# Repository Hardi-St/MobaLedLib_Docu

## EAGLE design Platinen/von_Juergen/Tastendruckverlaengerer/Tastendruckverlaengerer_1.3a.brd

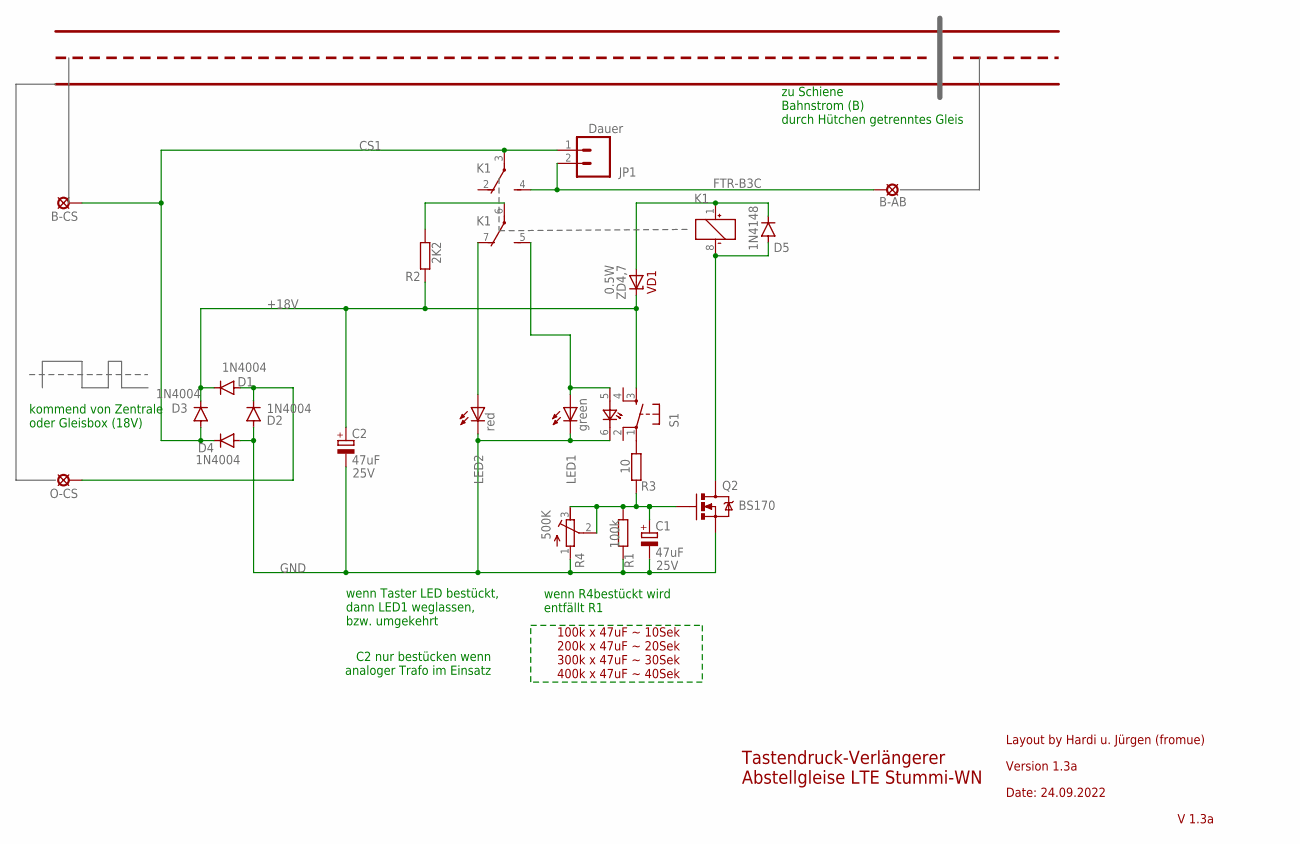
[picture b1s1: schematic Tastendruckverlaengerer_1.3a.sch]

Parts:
B-AB: SE14
B-CS: SE14
C1, C2: 47uF; TT2D5L
D1, D2, D3, D4: 1N4004; DO41-10A
D5: 1N4148; DO35-7
JP1: Dauer; 1X02
K1: FTR-B3C; FTR-B4C
LED1: green; LED3MM
LED2: red; LED3MM
O-CS: SE14
Q2: BS170; TO-92
R1: 100k; 0204/7
R2: 2K2; 0204/7
R3: 10; 0204/7
R4: 500K; RTRIM3296W
S1: TASTER_LEDTC-1198-B; TASTER_LED
VD1: ZD4,7; DIODES-ZENER_DO35-7; MOUSER ZF4.7

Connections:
+18V: C2.+, D1.C, D3.C, R2.2, S1.3 (S), VD1.C
CS1: B-CS.MP, D3.A, D4.C, JP1.1, K1.3
GND: C1.-, C2.-, D2.A, D4.A, LED1.K (C), LED2.K (C), Q2.3 (S), R1.2, R4.1 (A), S1.6 (-)
unnamed: K1.6, R2.1
unnamed: K1.5 (S), LED1.A, S1.5 (+)
unnamed: K1.7 (O), LED2.A
unnamed: D5.C, K1.1 (+), VD1.A
unnamed: C1.+, Q2.2 (G), R1.1, R3.2, R4.2 (S), R4.3 (E)
unnamed: D5.A, K1.8 (-), Q2.1 (D)
unnamed: D1.A, D2.C, O-CS.MP
unnamed: B-AB.MP, JP1.2, K1.4 (S)
TAST: R3.1, S1.1

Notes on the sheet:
kommend von Zentrale oder Gleisbox (18V)
zu Schiene Bahnstrom (B) durch Hütchen getrenntes Gleis
Tastendruck-Verlängerer Abstellgleise LTE Stummi-WN
Layout by Hardi u. Jürgen (fromue)
Version 1.3a
Date: 24.09.2022
V 1.3a
100k x 47uF ~ 10Sek 200k x 47uF ~ 20Sek 300k x 47uF ~ 30Sek 400k x 47uF ~ 40Sek
wenn R4bestückt wird entfällt R1
wenn Taster LED bestückt, dann LED1 weglassen, bzw. umgekehrt
C2 nur bestücken wenn analoger Trafo im Einsatz

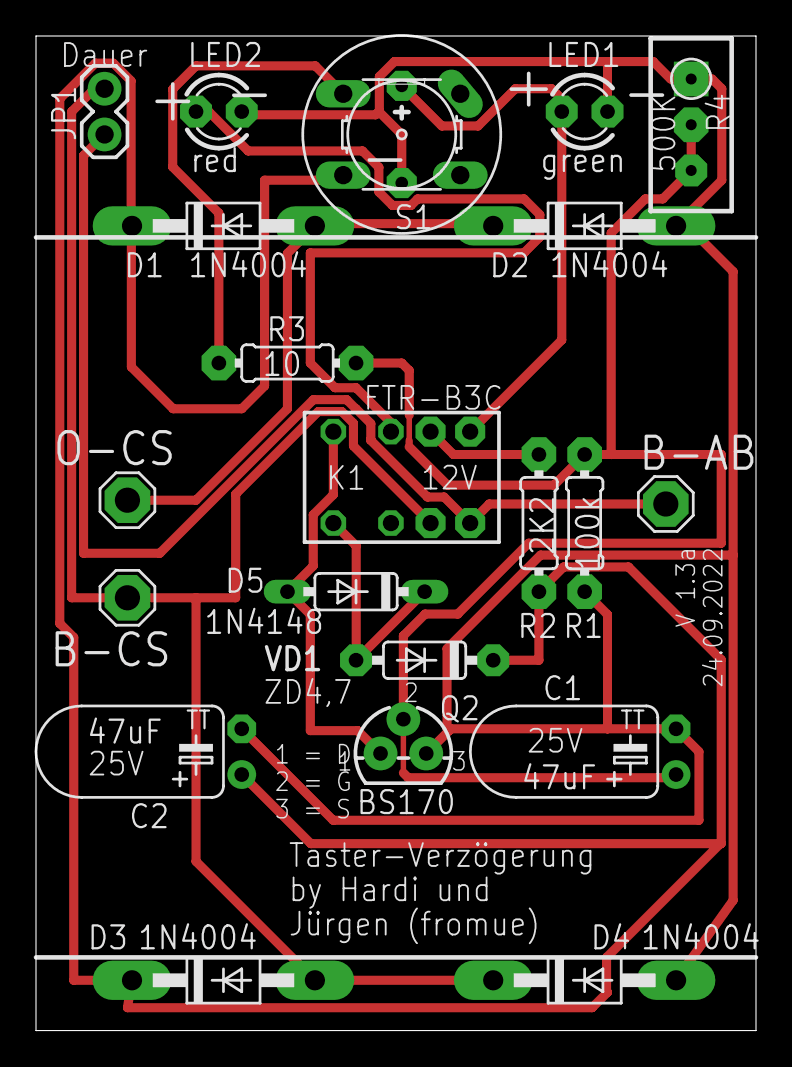
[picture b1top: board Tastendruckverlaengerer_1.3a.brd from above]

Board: 2 copper layers, 40.0 x 55.3 mm, 21 parts (0 on the bottom side), 12 nets.

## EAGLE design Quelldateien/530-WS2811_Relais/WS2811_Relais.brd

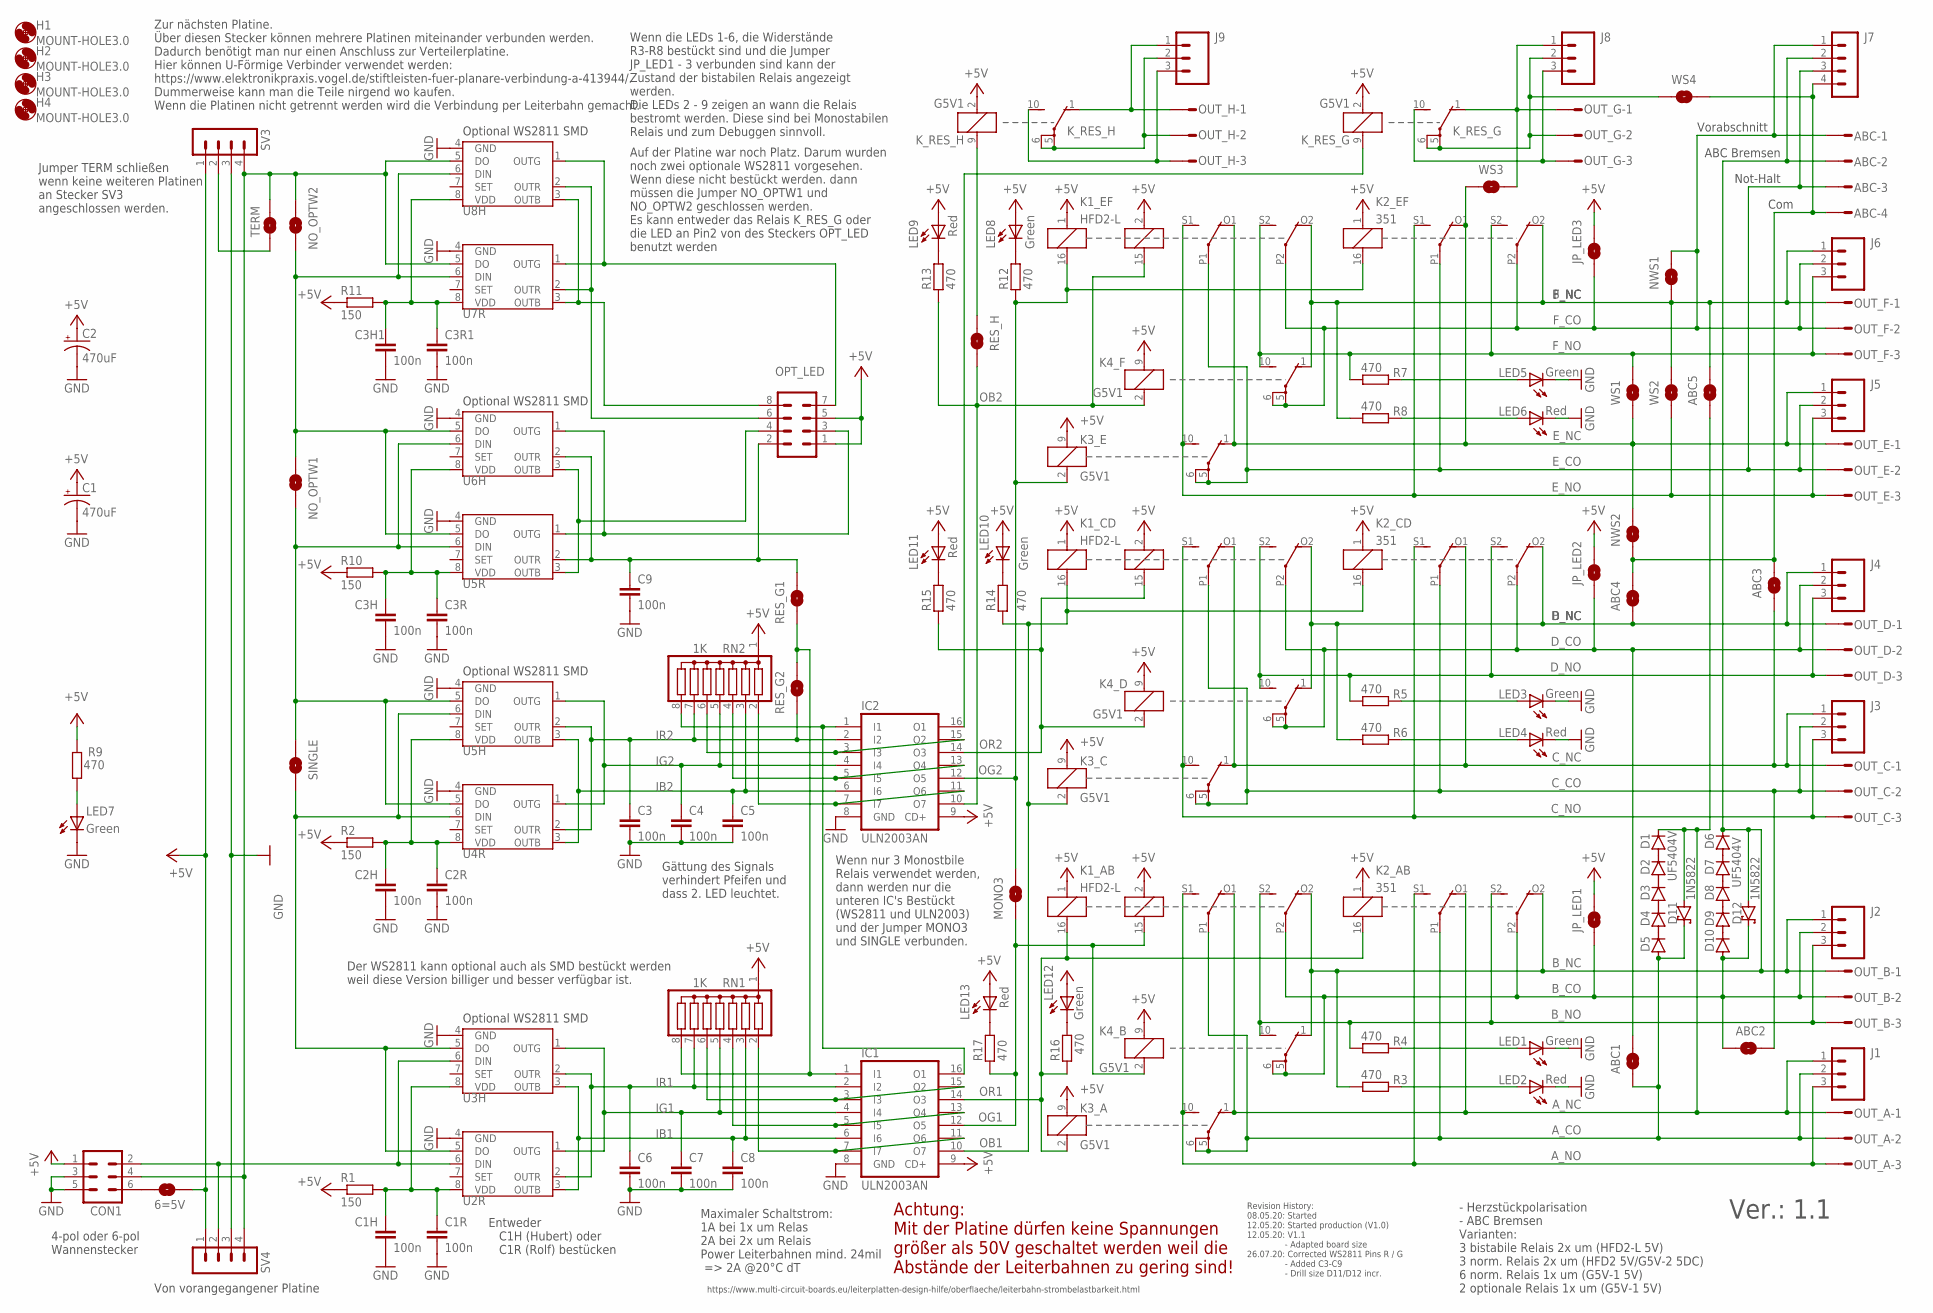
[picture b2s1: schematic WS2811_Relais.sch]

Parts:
6=5V: SOLDERJUMPERNO; SJ_2S-NO
ABC: STL1550-4ON_BOARD; STL1550-4_ON_BOARD
ABC1, ABC2, ABC3, ABC4, ABC5: SOLDERJUMPERNO; SJ_2S-NO
C1, C2: 470uF; SPARKFUN-CAPACITORS_CPOL-RADIAL-100UF-25V
C1H, C2H, C3H, C3H1: 100n; C1206
C1R, C2R, C3, C3R, C3R1, C4, C5, C6, C7, C8, C9: 100n; C025-024X044
CON1: ML6
D1, D2, D3, D4, D5, D6, D7, D8, D9, D10: UF5404V; DO201-15-V
D11, D12: 1N5822; DO41-7.6
H1, H2, H3, H4: MOUNT-HOLE3.0; 3,0
IC1, IC2: ULN2003AN; DIL16
J1, J2, J3, J4, J5, J6, J8, J9: M03PTH; 1X03
J7: MA04-1
JP_LED1, JP_LED2, JP_LED3: SOLDERJUMPERNO; SJ_2S-NO
K1_AB, K1_CD, K1_EF: HFD2-L
K2_AB, K2_CD, K2_EF: 351
K3_A, K3_C, K3_E, K4_B, K4_D, K4_F: G5V1
K_RES_G: G5V1
K_RES_H: G5V1
LED1, LED3, LED5, LED7, LED8, LED10, LED12: Green; LED3MM
LED2, LED4, LED6, LED9, LED11, LED13: Red; LED3MM
MONO3: SOLDERJUMPERNO; SJ_2S-NO
NO_OPTW1, NO_OPTW2: SOLDERJUMPERNO; SJ_2S-NO
NWS1, NWS2: SOLDERJUMPERNO; SJ_2S-NO
OPT_LED: CON-HARTING-ML_ML08
OUT_A: STL1550-3
OUT_B: STL1550-3
OUT_C: STL1550-3
OUT_D: STL1550-3
OUT_E: STL1550-3
OUT_F: STL1550-3
OUT_G: STL1550-3
OUT_H: STL1550-3
R1, R2, R10, R11: 150; RCL_0207/2V
R3, R4, R5, R6, R7, R8, R9, R12, R13, R14, R15, R16, R17: 470; 0204/2V
RES_G1, RES_G2: SOLDERJUMPERNO; SJ_2S-NO
RES_H: SOLDERJUMPERNO; SJ_2S-NO
RN1, RN2: 1K; SIL8
SINGLE: SOLDERJUMPERNO; SJ_2S-NO
SV3, SV4: MA04-1
TERM: SOLDERJUMPERNO; SJ_2S-NO
U2R, U4R, U5R, U7R: TINY45-20-DIP; S3PO_MODUL_WS2811_SOUND_MP3-TF-16P_WS2811_AND_ATTINY_WS2811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
U3H, U5H, U6H, U8H: WS2811 SOT-8; SOP8
WS1, WS2, WS3, WS4: SOLDERJUMPERNO; SJ_2S-NO

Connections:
$N100: IC2.7 (I7), IC2.11 (O6), RN2.2
+5V: 6=5V.2, C1.1 (+), C2.1 (+), CON1.1, IC1.9 (CD+), IC2.9 (CD+), JP_LED1.2, JP_LED2.2, JP_LED3.2, K1_AB.1, K1_AB.2 (3), K1_CD.1, K1_CD.2 (3), K1_EF.1, K1_EF.2 (3), K2_AB.1, K2_CD.1, K2_EF.1, K3_A.9 (2), K3_C.9 (2), K3_E.9 (2), K4_B.9 (2), K4_D.9 (2), K4_F.9 (2), K_RES_G.2 (1), K_RES_H.2 (1), LED8.A, LED9.A, LED10.A, LED11.A, LED12.A, LED13.A, OPT_LED.1, OPT_LED.5, R1.1, R2.1, R9.1, R10.1, R11.1, RN1.1, RN2.1, SV3.1, SV4.1
A_CO: ABC1.1, D5.A, D11.C, J1.2, K1_AB.P1, K2_AB.P1, K3_A.5, K3_A.6, OUT_A.2
A_NC: ABC5.2, D1.C, D11.A, J1.1, K1_AB.O1 (O), K2_AB.O1 (O), K3_A.1 (O), OUT_A.1
A_NO: J1.3, K1_AB.S1 (S), K2_AB.S1 (S), K3_A.10 (S), OUT_A.3
B_CO: ABC2.1, D10.A, D12.C, J2.2, JP_LED1.1, K1_AB.P2, K2_AB.P2, K4_B.5, K4_B.6, OUT_B.2
B_NC: ABC.2, D6.C, D12.A, J2.1, J7.2, K1_AB.O2 (O), K2_AB.O2 (O), K4_B.1 (O), OUT_B.1, R3.2
B_NO: J2.3, K1_AB.S2 (S), K2_AB.S2 (S), K4_B.10 (S), OUT_B.3, R4.2
C_CO: ABC2.2, J3.2, K1_CD.P1, K2_CD.P1, K3_C.5, K3_C.6, OUT_C.2
C_NC: ABC3.2, J3.1, K1_CD.O1 (O), K2_CD.O1 (O), K3_C.1 (O), OUT_C.1
C_NO: J3.3, K1_CD.S1 (S), K2_CD.S1 (S), K3_C.10 (S), OUT_C.3
D_CO: ABC1.2, J4.2, JP_LED2.1, K1_CD.P2, K2_CD.P2, K4_D.5, K4_D.6, OUT_D.2
D_NC: ABC4.2, J4.1, K1_CD.O2 (O), K2_CD.O2 (O), K4_D.1 (O), OUT_D.1, R6.2
D_NO: J4.3, K1_CD.S2 (S), K2_CD.S2 (S), K4_D.10 (S), OUT_D.3, R5.2
E_CO: ABC.3, J5.2, J7.3, K1_EF.P1, K2_EF.P1, K3_E.5, K3_E.6, OUT_E.2
E_NC: J5.1, K1_EF.O1 (O), K2_EF.O1 (O), K3_E.1 (O), NWS2.1, OUT_E.1, WS1.2, WS3.2
E_NO: J5.3, K1_EF.S1 (S), K2_EF.S1 (S), K3_E.10 (S), OUT_E.3, WS2.2
F_CO: ABC.1, J6.2, J7.1, JP_LED3.1, K1_EF.P2, K2_EF.P2, K4_F.5, K4_F.6, NWS1.1, OUT_F.2
F_NC: ABC5.1, J6.1, K1_EF.O2 (O), K2_EF.O2 (O), K4_F.1 (O), NWS1.2, OUT_F.1, R8.2, WS2.1
F_NO: J6.3, K1_EF.S2 (S), K2_EF.S2 (S), K4_F.10 (S), OUT_F.3, R7.2, WS1.1
GND: C1.2 (-), C1H.2, C1R.2, C2.2 (-), C2H.2, C2R.2, C3.2, C3H.2, C3H1.2, C3R.2, C3R1.2, C4.2, C5.2, C6.2, C7.2, C8.2, C9.2, CON1.3, CON1.5, IC1.8 (GND), IC2.8 (GND), LED1.K (C), LED2.K (C), LED3.K (C), LED4.K (C), LED5.K (C), LED6.K (C), LED7.K (C), SV3.3, SV4.3, U2R.4 (GND), U3H.4 (GND), U4R.4 (GND), U5H.4 (GND), U5R.4 (GND), U6H.4 (GND), U7R.4 (GND), U8H.4 (GND)
IB1: C8.1, IC1.6 (I6), RN1.3, U2R.3 (OUTB), U3H.3 (OUTB)
IB2: C5.1, IC2.6 (I6), RN2.3, U4R.3 (OUTB), U5H.3 (OUTB)
IB3: OPT_LED.4, U5R.3 (OUTB), U6H.3 (OUTB)
IB4: OPT_LED.8, U7R.3 (OUTB), U8H.3 (OUTB)
IG1: C7.1, IC1.4 (I4), RN1.5, U2R.1 (OUTG), U3H.1 (OUTG)
IG2: C4.1, IC2.4 (I4), RN2.5, U4R.1 (OUTG), U5H.1 (OUTG)
IG3: OPT_LED.3, U5R.1 (OUTG), U6H.1 (OUTG)
IG4: OPT_LED.7, U7R.1 (OUTG), U8H.1 (OUTG)
IR1: C6.1, IC1.2 (I2), RN1.7, U2R.2 (OUTR), U3H.2 (OUTR)
IR2: C3.1, IC2.2 (I2), RES_G2.2, RN2.7, U4R.2 (OUTR), U5H.2 (OUTR)
IR3: IC1.1 (I1), RES_G1.2, RES_G2.1, RN1.8
IR4: OPT_LED.6, U7R.2 (OUTR), U8H.2 (OUTR)
unnamed: CON1.2, SV4.2, U2R.6 (DIN), U3H.6 (DIN)
unnamed: LED2.A, R3.1
unnamed: CON1.4, NO_OPTW2.1, SV3.4, SV4.4, TERM.1, U7R.5 (DO), U8H.5 (DO)
unnamed: C1H.1, C1R.1, R1.2, U2R.8 (VDD), U3H.8 (VDD)
unnamed: LED1.A, R4.1
unnamed: 6=5V.1, CON1.6
unnamed: IC1.7 (I7), IC1.11 (O6), RN1.2
unnamed: LED4.A, R6.1
unnamed: IC1.3 (I3), IC1.15 (O2), RN1.6
unnamed: SV3.2, TERM.2
unnamed: IC1.5 (I5), IC1.13 (O4), RN1.4
unnamed: LED3.A, R5.1
unnamed: C2H.1, C2R.1, R2.2, U4R.8 (VDD), U5H.8 (VDD)
unnamed: LED6.A, R8.1
unnamed: LED5.A, R7.1
unnamed: D1.A, D2.C
unnamed: IC1.16 (O1), IC2.1 (I1), RN2.8
unnamed: IC2.5 (I5), IC2.13 (O4), RN2.4
unnamed: D2.A, D3.C
unnamed: SINGLE.2, U2R.5 (DO), U3H.5 (DO), U4R.6 (DIN), U5H.6 (DIN)
unnamed: D3.A, D4.C
unnamed: LED7.A, R9.2
unnamed: D4.A, D5.C
unnamed: D7.A, D8.C
unnamed: D8.A, D9.C
unnamed: D9.A, D10.C
unnamed: D6.A, D7.C
unnamed: C9.1, OPT_LED.2, RES_G1.1, U5R.2 (OUTR), U6H.2 (OUTR)
unnamed: IC2.3 (I3), IC2.15 (O2), RN2.6
unnamed: J8.2, K_RES_G.5, K_RES_G.6, OUT_G.2, WS4.2
unnamed: IC2.16 (O1), K_RES_G.9 (2)
unnamed: J8.1, K_RES_G.1 (O), OUT_G.1, WS3.1
unnamed: J8.3, K_RES_G.10 (S), OUT_G.3
unnamed: NO_OPTW1.1, NO_OPTW2.2, U5R.5 (DO), U6H.5 (DO), U7R.6 (DIN), U8H.6 (DIN)
unnamed: C3H.1, C3R.1, R10.2, U5R.8 (VDD), U6H.8 (VDD)
unnamed: J9.2, K_RES_H.5, K_RES_H.6, OUT_H.2
unnamed: NO_OPTW1.2, SINGLE.1, U4R.5 (DO), U5H.5 (DO), U5R.6 (DIN), U6H.6 (DIN)
unnamed: J9.3, K_RES_H.10 (S), OUT_H.3
unnamed: C3H1.1, C3R1.1, R11.2, U7R.8 (VDD), U8H.8 (VDD)
unnamed: J9.1, K_RES_H.1 (O), OUT_H.1
unnamed: K_RES_H.9 (2), RES_H.2
unnamed: LED8.K (C), R12.1
unnamed: LED9.K (C), R13.1
unnamed: LED10.K (C), R14.1
unnamed: LED11.K (C), R15.1
unnamed: LED12.K (C), R16.1
unnamed: LED13.K (C), R17.1
unnamed: ABC.4, ABC3.1, ABC4.1, J7.4, NWS2.2, WS4.1
OB1: IC1.10 (O7), K1_CD.16 (2), K2_CD.16 (2), K3_C.2 (1), R14.2
OB2: IC2.10 (O7), K1_EF.15 (4), K4_F.2 (1), R13.2, RES_H.1
OG1: IC1.12 (O5), K1_AB.15 (4), K4_B.2 (1), MONO3.2, R17.2
OG2: IC2.12 (O5), K1_EF.16 (2), K2_EF.16 (2), K3_E.2 (1), MONO3.1, R12.2
OR1: IC1.14 (O3), K1_AB.16 (2), K2_AB.16 (2), K3_A.2 (1), R16.2
OR2: IC2.14 (O3), K1_CD.15 (4), K4_D.2 (1), R15.2

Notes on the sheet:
4-pol oder 6-pol Wannenstecker
Optional WS2811 SMD
Zur nächsten Platine. Über diesen Stecker können mehrere Platinen miteinander verbunden werden. Dadurch benötigt man nur einen Anschluss zur Verteilerplatine. Hier können U-Förmige Verbinder verwendet werden: https://www.elektronikpraxis.vogel.de/stiftleisten-fuer-planare-verbindung-a-413944/. Dumm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
Von vorangegangener Platine
Der WS2811 kann optional auch als SMD bestückt werden weil diese Version billiger und besser verfügbar ist.
Ver.: 1.1
Entweder C1H (Hubert) oder C1R (Rolf) bestücken
Jumper TERM schließen wenn keine weiteren Platinen an Stecker SV3 angeschlossen werden.
Revision History: 08.05.20: Started 12.05.20: Started production (V1.0) 12.05.20: V1.1 - Adapted board size 26.07.20: Corrected WS2811 Pins R / G - Added C3-C9 - Drill size D11/D12 incr.
Vorabschnitt
ABC Bremsen
Not-Halt
Wenn nur 3 Monostbile Relais verwendet werden, dann werden nur die unteren IC's Bestückt (WS2811 und ULN2003) und der Jumper MONO3 und SINGLE verbunden.
- Herzstückpolarisation - ABC Bremsen Varianten: 3 bistabile Relais 2x um (HFD2-L 5V) 3 norm. Relais 2x um (HFD2 5V/G5V-2 5DC) 6 norm. Relais 1x um (G5V-1 5V) 2 optionale Relais 1x um (G5V-1 5V)
Auf der Platine war noch Platz. Darum wurden noch zwei optionale WS2811 vorgesehen. Wenn diese nicht bestückt werden. dann müssen die Jumper NO_OPTW1 und NO_OPTW2 geschlossen werden. Es kann entweder das Relais K_RES_G oder die LED an Pin2 von des Steckers OPT_LED benutzt werden
Com
Achtung: Mit der Platine dürfen keine Spannungen größer als 50V geschaltet werden weil die Abstände der Leiterbahnen zu gering sind!
Maximaler Schaltstrom: 1A bei 1x um Relas 2A bei 2x um Relais Power Leiterbahnen mind. 24mil => 2A @20°C dT
https://www.multi-circuit-boards.eu/leiterplatten-design-hilfe/oberflaeche/leiterbahn-strombelastbarkeit.html
Gättung des Signals verhindert Pfeifen und dass 2. LED leuchtet.
Wenn die LEDs 1-6, die Widerstände R3-R8 bestückt sind und die Jumper JP_LED1 - 3 verbunden sind kann der Zustand der bistabilen Relais angezeigt werden. Die LEDs 2 - 9 zeigen an wann die Relais bestromt werden. Diese sind bei Monostabilen Relais und zum Debuggen sinnvoll.

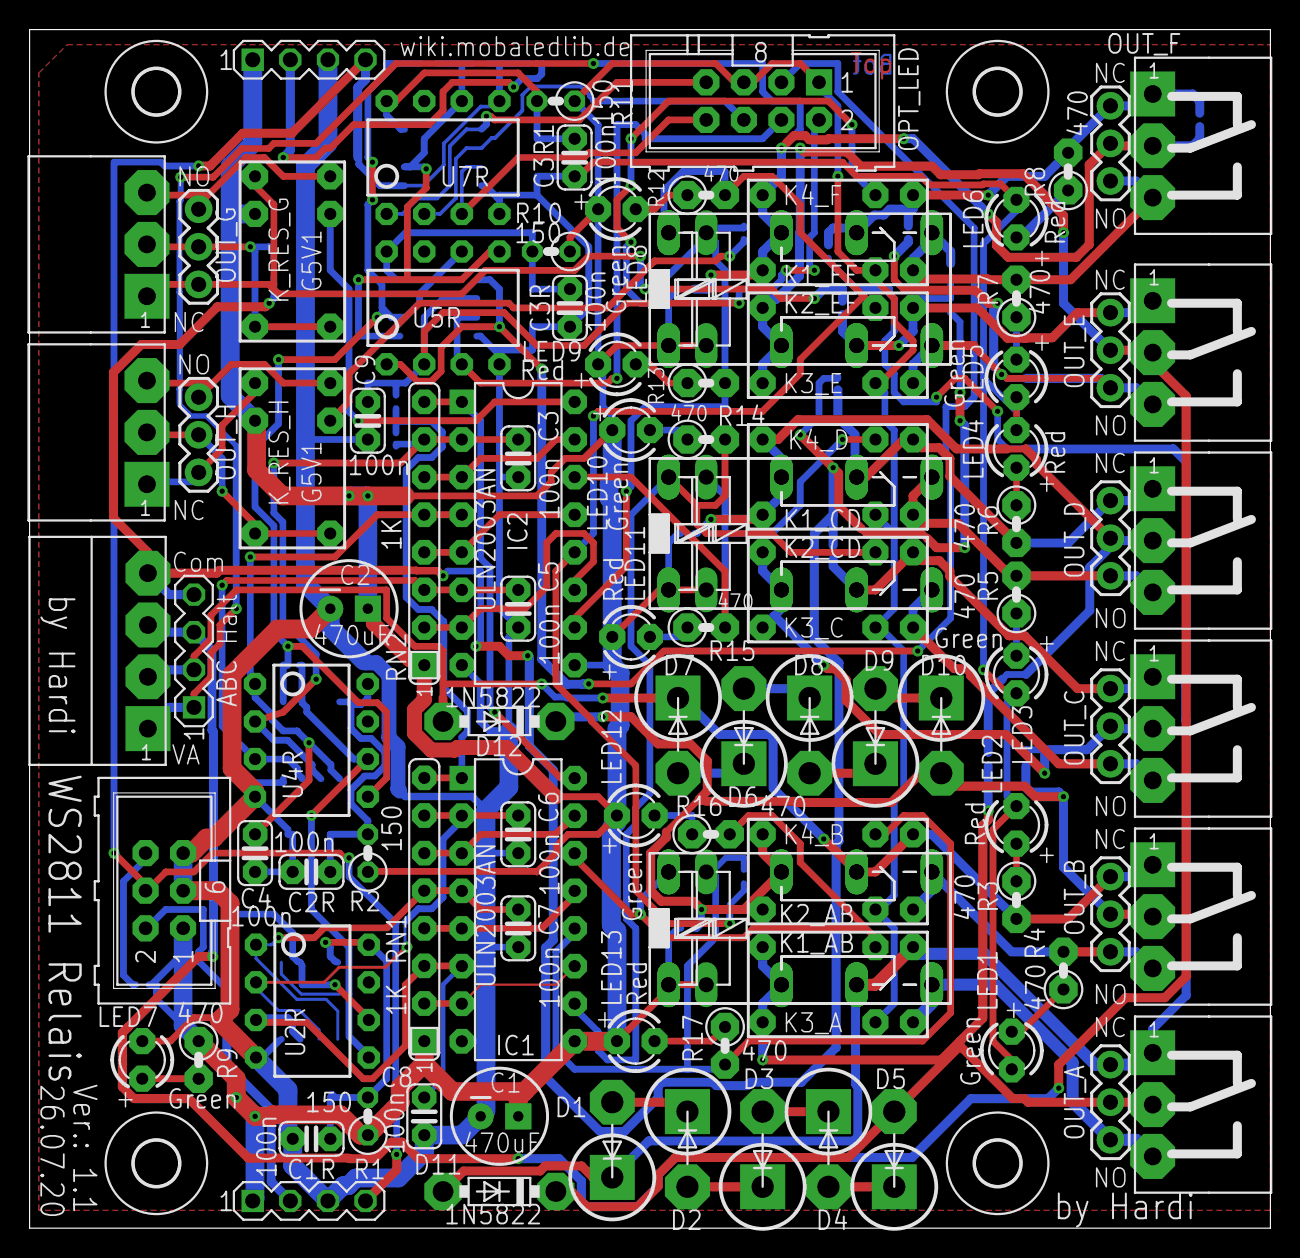
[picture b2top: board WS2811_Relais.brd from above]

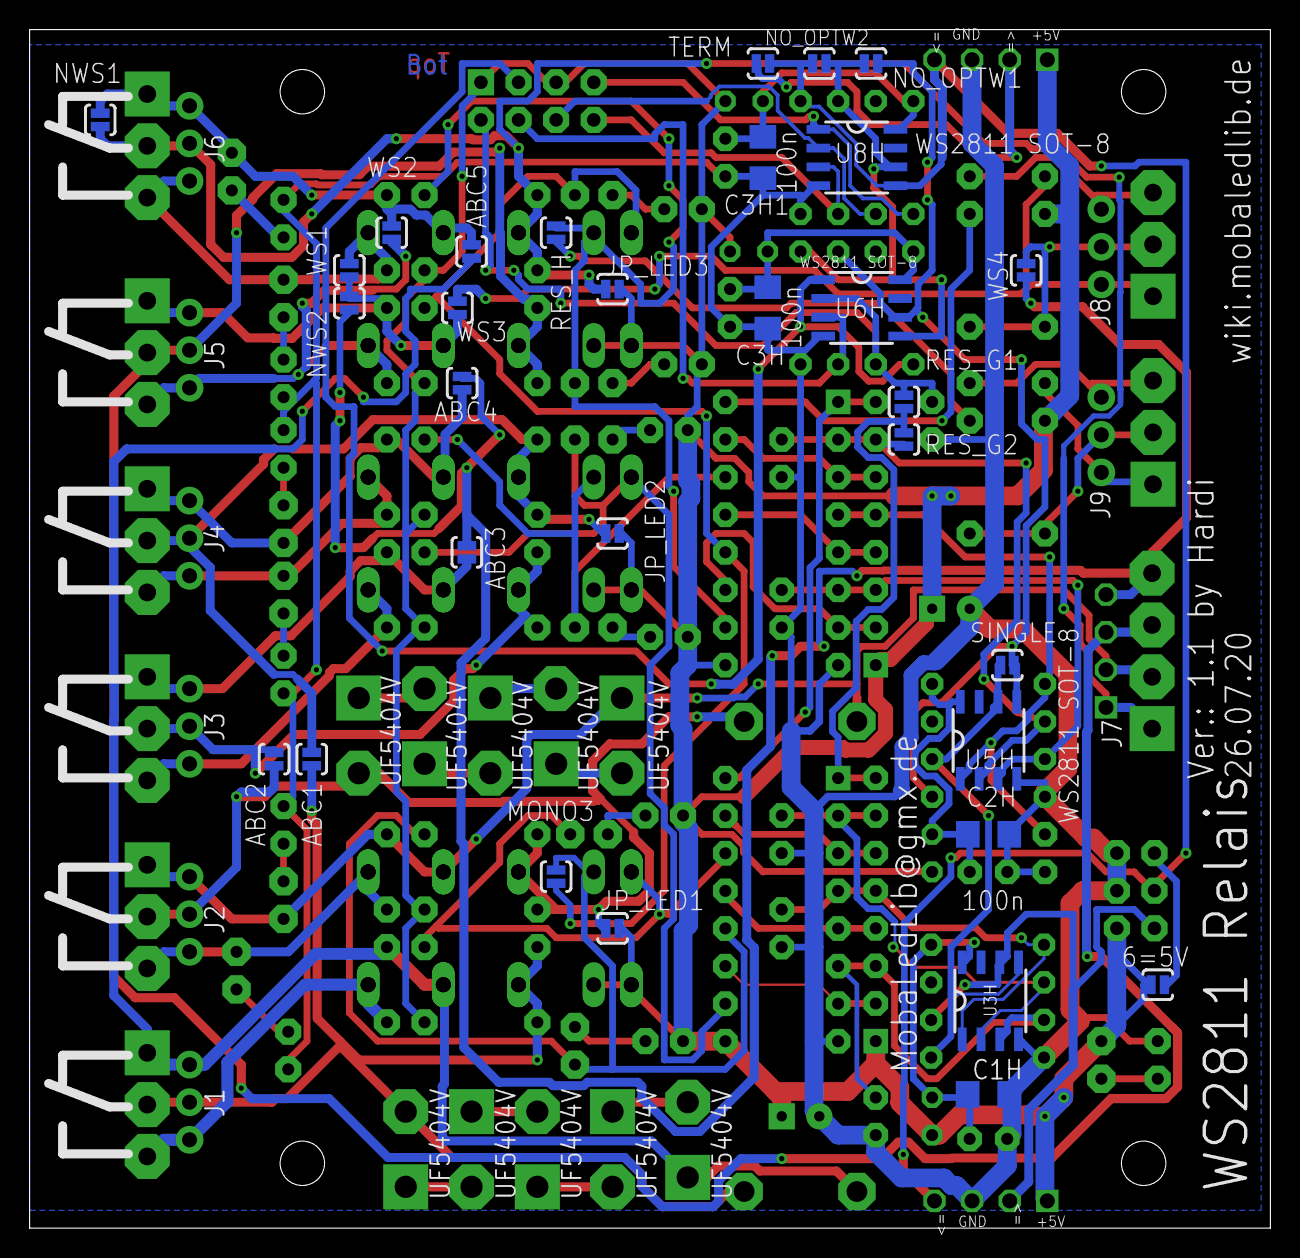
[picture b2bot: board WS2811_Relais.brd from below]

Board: 2 copper layers, 83.8 x 81.0 mm, 134 parts (31 on the bottom side), 87 nets.

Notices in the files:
parts and their libraries:
SparkFun-DiscreteSemi: Licensing: Creative Commons ShareAlike 4.0 International - https://creativecommons.org/licenses/by-sa/4.0
